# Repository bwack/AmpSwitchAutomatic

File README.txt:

Amp Switch Automatic,
6 amplifiers connected to one pair of stereo speakers with
automatic switching.

Realized with 1970-80s digital logic technology on two stripboards, and
a project box with 28 speaker terminals on it and a 5V power input.

Cheepo auto 1:1 600:600 ohm audio transformers were used to galvanically
isolate the amplifiers, and to pass audio to the detector circuits (lm339).
The relays switch the amplifiers in one at a time. If there is audio on
more than one amplifier, the amp switch sticks to the currently switched amp,
just to keep the box from switching too much. It is not intended to mix,
just switch though.

Bwack, 2017

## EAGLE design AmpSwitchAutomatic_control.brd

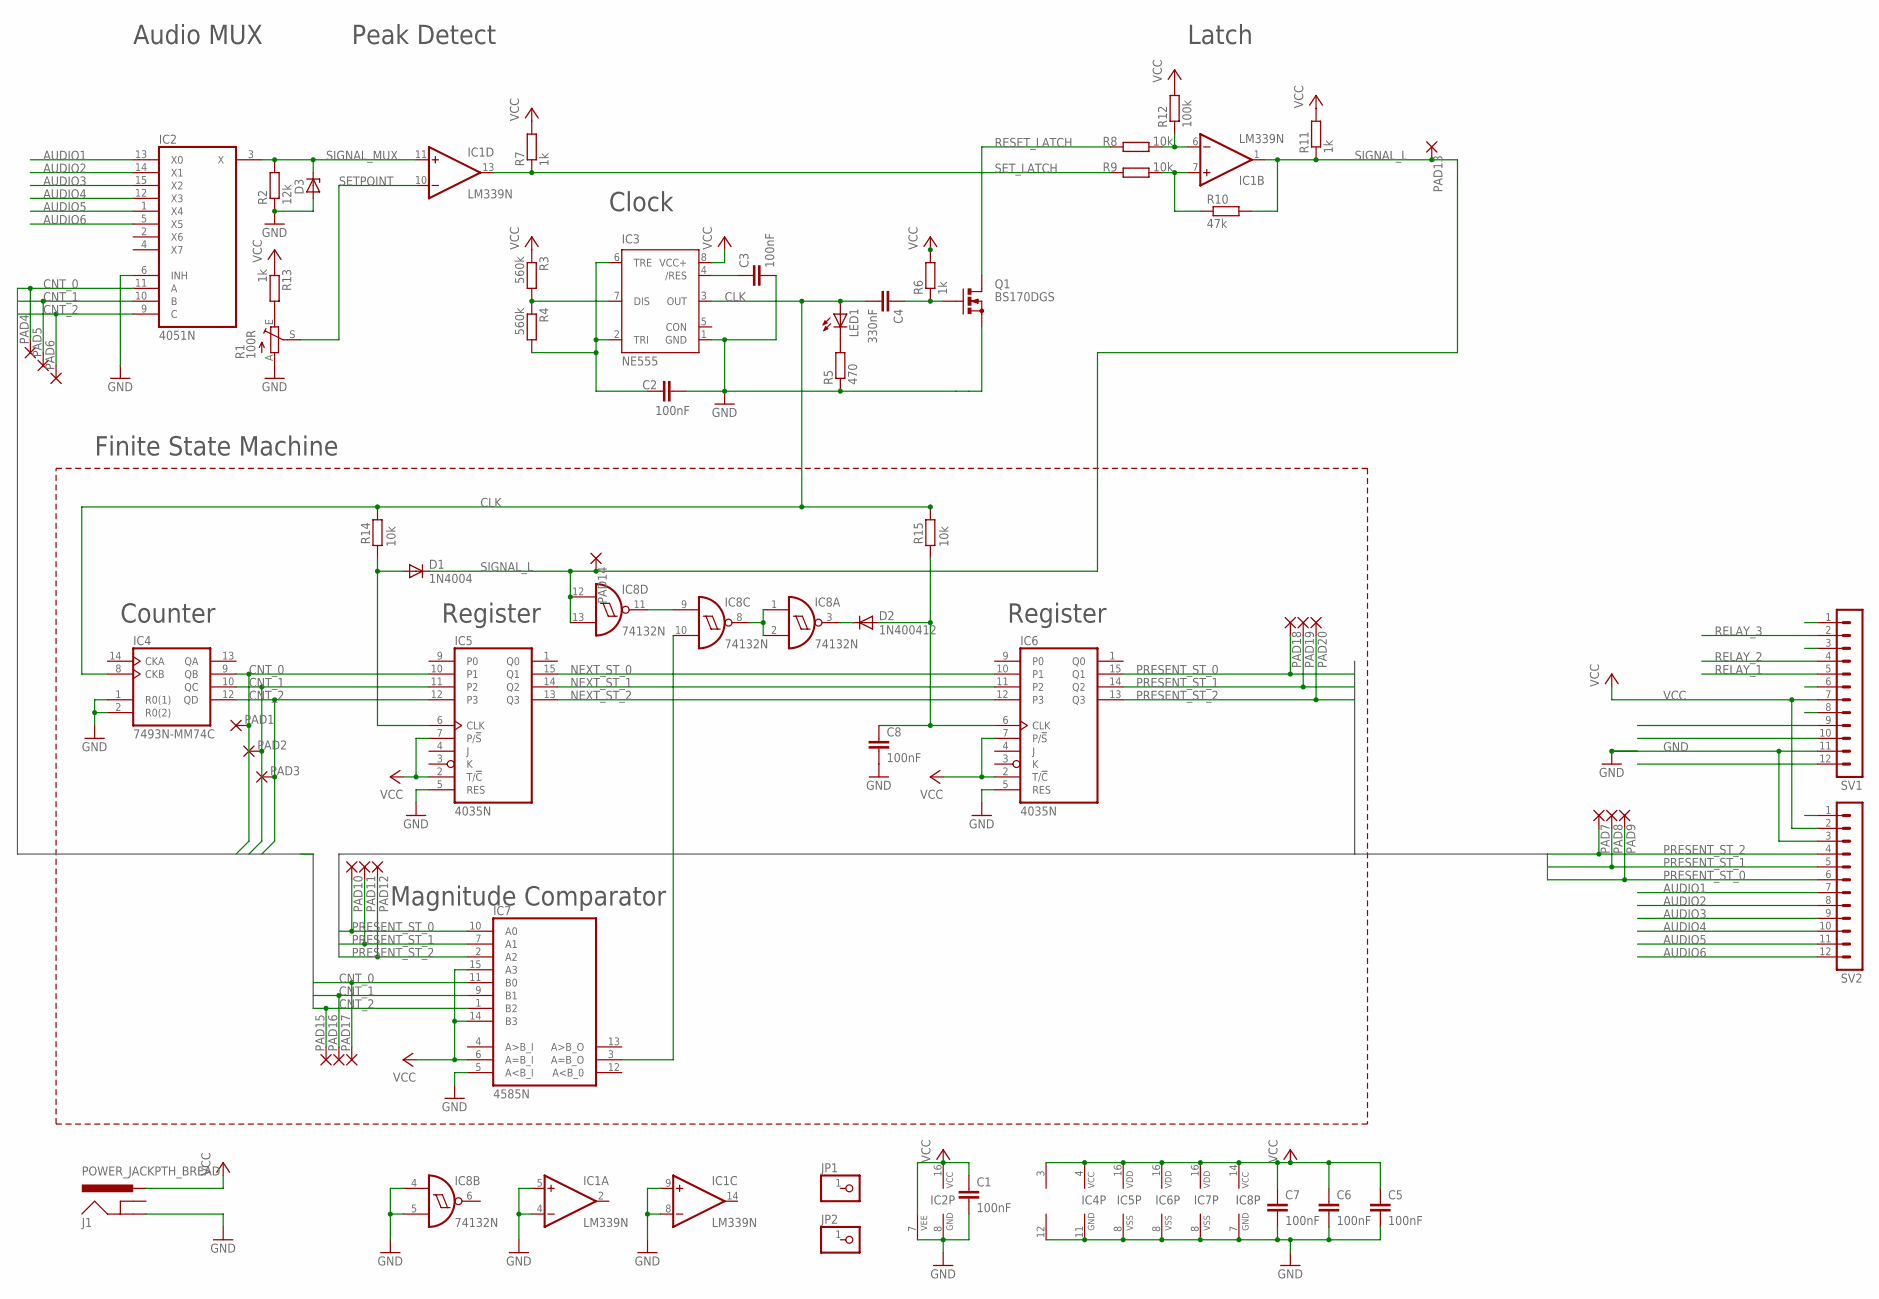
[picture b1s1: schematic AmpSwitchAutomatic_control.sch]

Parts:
C1, C5, C6, C7: 100nF; C025-025X050
C2, C3: 100nF; C025-024X044
C4: 330nF; C075-032X103
C8: 100nF; C050-025X075
D1: 1N4004; DO41-10
D2: 1N400412; DO41-12
D3: ZENER-DIODEDO35Z10; DO35Z10
IC1: LM339N; DIL14
IC2: 4051N; DIL16
IC3: NE555; DIL-08
IC4: 7493N-MM74C; DIL14
IC5, IC6: 4035N; DIL16
IC7: 4585N; DIL16
IC8: 74132N; DIL14
J1: POWER_JACKPTH_BREAD; POWER_JACK_PTH_BREAD
JP1, JP2: PINHD-1X1; 1X01
LED1: LED5MM
PAD1, PAD2, PAD3, PAD4, PAD5, PAD6, PAD7, PAD8, PAD9, PAD10, PAD11, PAD12, PAD13, PAD14, PAD15, PAD16, PAD17, PAD18, PAD19, PAD20: WIREPAD1,6/0,9; 1,6/0,9
Q1: BS170DGS; TO92-LINE
R1: 100R; B25P
R2: 12k; 0207/10
R3, R4: 560k; 0207/2V
R5: 470; 0207/15
R6: 1k; 0207/12
R7, R11: 1k; 0207/5V
R8: 10k; 0207/5V
R9: 10k; 0207/15
R10: 47k; 0207/15
R12: 100k; 0207/7
R13: 1k; 0207/7
R14: 10k; 0207/7
R15: 10k; 0207/2V
SV1, SV2: MA12-1

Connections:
AUDIO1: IC2.13 (X0), SV2.7
AUDIO2: IC2.14 (X1), SV2.8
AUDIO3: IC2.15 (X2), SV2.9
AUDIO4: IC2.12 (X3), SV2.10
AUDIO5: IC2.1 (X4), SV2.11
AUDIO6: IC2.5 (X5), SV2.12
CLK: C4.2, IC3.3 (OUT), IC4.8 (CKB), LED1.A, R14.2, R15.2
CNT_0: IC2.11 (A), IC4.9 (QB), IC5.10 (P1), IC7.11 (B0), PAD1.1, PAD4.1, PAD17.1
CNT_1: IC2.10 (B), IC4.10 (QC), IC5.11 (P2), IC7.9 (B1), PAD2.1, PAD5.1, PAD16.1
CNT_2: IC2.9 (C), IC4.12 (QD), IC5.12 (P3), IC7.1 (B2), PAD3.1, PAD6.1, PAD15.1
GND: C1.2, C2.2, C3.2, C5.2, C6.2, C7.2, C8.2, D3.A, IC1.4 (-IN), IC1.5 (+IN), IC1.8 (-IN), IC1.9 (+IN), IC1.12 (GND), IC2.6 (INH), IC2.7 (VEE), IC2.8 (GND), IC3.1 (GND), IC4.1 (R0(1)), IC4.2 (R0(2)), IC4.11 (GND), IC5.5 (RES), IC5.8 (VSS), IC6.5 (RES), IC6.8 (VSS), IC7.5 (A<B_I), IC7.8 (VSS), IC8.4 (I0), IC8.5 (I1), IC8.7 (GND), J1.GND, Q1.3 (S), R1.A, R2.1, R5.1, SV1.11, SV2.3
unnamed: R1.E, R13.2
unnamed: IC3.7 (DIS), R3.2, R4.1
unnamed: C2.1, IC3.2 (TRI), IC3.6 (TRE), R4.2
unnamed: LED1.K (C), R5.2
unnamed: C4.1, Q1.2 (G), R6.1
unnamed: IC1.6 (-IN), R8.2, R12.1
unnamed: IC1.7 (+IN), R9.2, R10.1
unnamed: C3.1, IC3.4 (/RES)
unnamed: D1.A, IC5.6 (CLK), R14.1
unnamed: D2.C, IC8.3 (O)
unnamed: C8.1, D2.A, IC6.6 (CLK), R15.1
unnamed: IC7.3 (A=B_O), IC8.10 (I1)
unnamed: IC8.1 (I0), IC8.2 (I1), IC8.8 (O)
unnamed: IC8.9 (I0), IC8.11 (O)
NEXT_ST_0: IC5.15 (Q1), IC6.10 (P1)
NEXT_ST_1: IC5.14 (Q2), IC6.11 (P2)
NEXT_ST_2: IC5.13 (Q3), IC6.12 (P3)
PRESENT_ST_0: IC6.15 (Q1), IC7.10 (A0), PAD9.1, PAD10.1, PAD18.1, SV2.6
PRESENT_ST_1: IC6.14 (Q2), IC7.7 (A1), PAD8.1, PAD11.1, PAD19.1, SV2.5
PRESENT_ST_2: IC6.13 (Q3), IC7.2 (A2), PAD7.1, PAD12.1, PAD20.1, SV2.4
RELAY_1: SV1.5
RELAY_2: SV1.4
RELAY_3: SV1.2
RESET_LATCH: Q1.1 (D), R8.1
SETPOINT: IC1.10 (-IN), R1.S
SET_LATCH: IC1.13 (OUT), R7.1, R9.1
SIGNAL_L: D1.C, IC1.1 (OUT), IC8.12 (I0), IC8.13 (I1), PAD13.1, PAD14.1, R10.2, R11.1
SIGNAL_MUX: D3.C, IC1.11 (+IN), IC2.3 (X), R2.2
VCC: C1.1, C5.1, C6.1, C7.1, IC1.3 (V+), IC2.16 (VCC), IC3.8 (VCC+), IC4.4 (VCC), IC5.2 (T/!C), IC5.7 (P/!S), IC5.16 (VDD), IC6.2 (T/!C), IC6.7 (P/!S), IC6.16 (VDD), IC7.6 (A=B_I), IC7.14 (B3), IC7.15 (A3), IC7.16 (VDD), IC8.14 (VCC), J1.PWR, R3.1, R6.2, R7.2, R11.2, R12.2, R13.1, SV1.7, SV2.2

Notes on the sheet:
Audio MUX
Peak Detect
Latch
Clock
Finite State Machine
Counter
Register
Magnitude Comparator

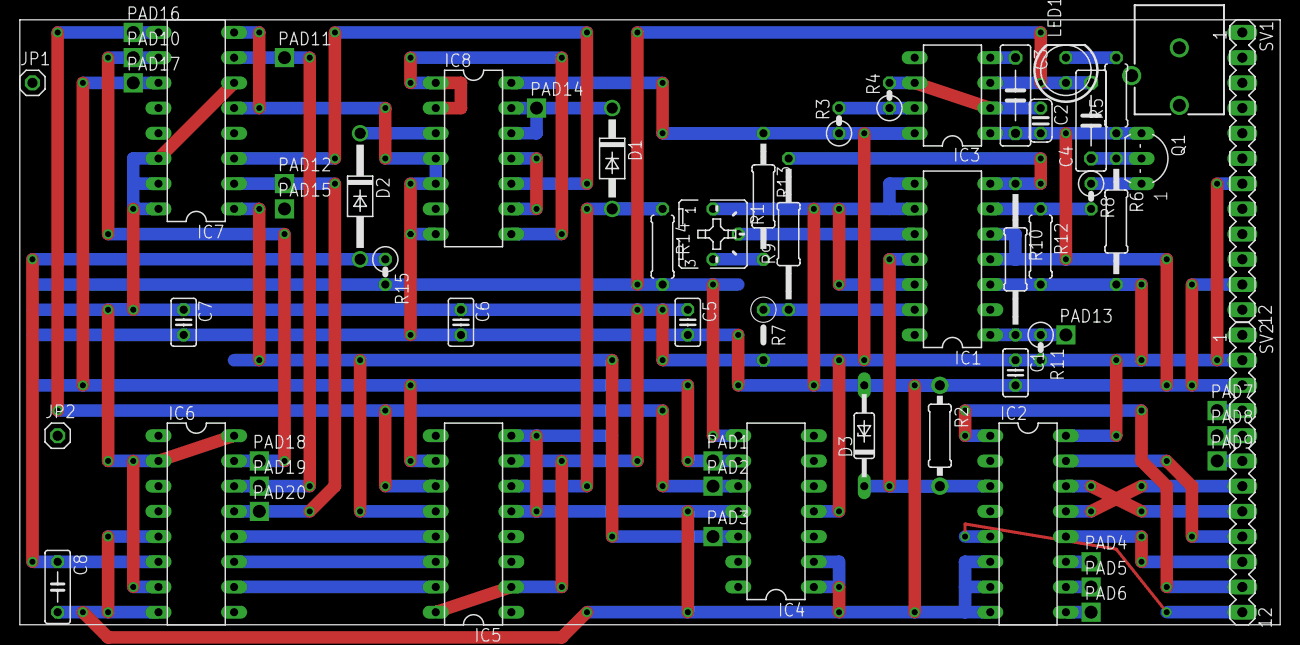
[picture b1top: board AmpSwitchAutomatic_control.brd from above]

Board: 2 copper layers, 127.0 x 61.0 mm, 61 parts (0 on the bottom side), 37 nets.

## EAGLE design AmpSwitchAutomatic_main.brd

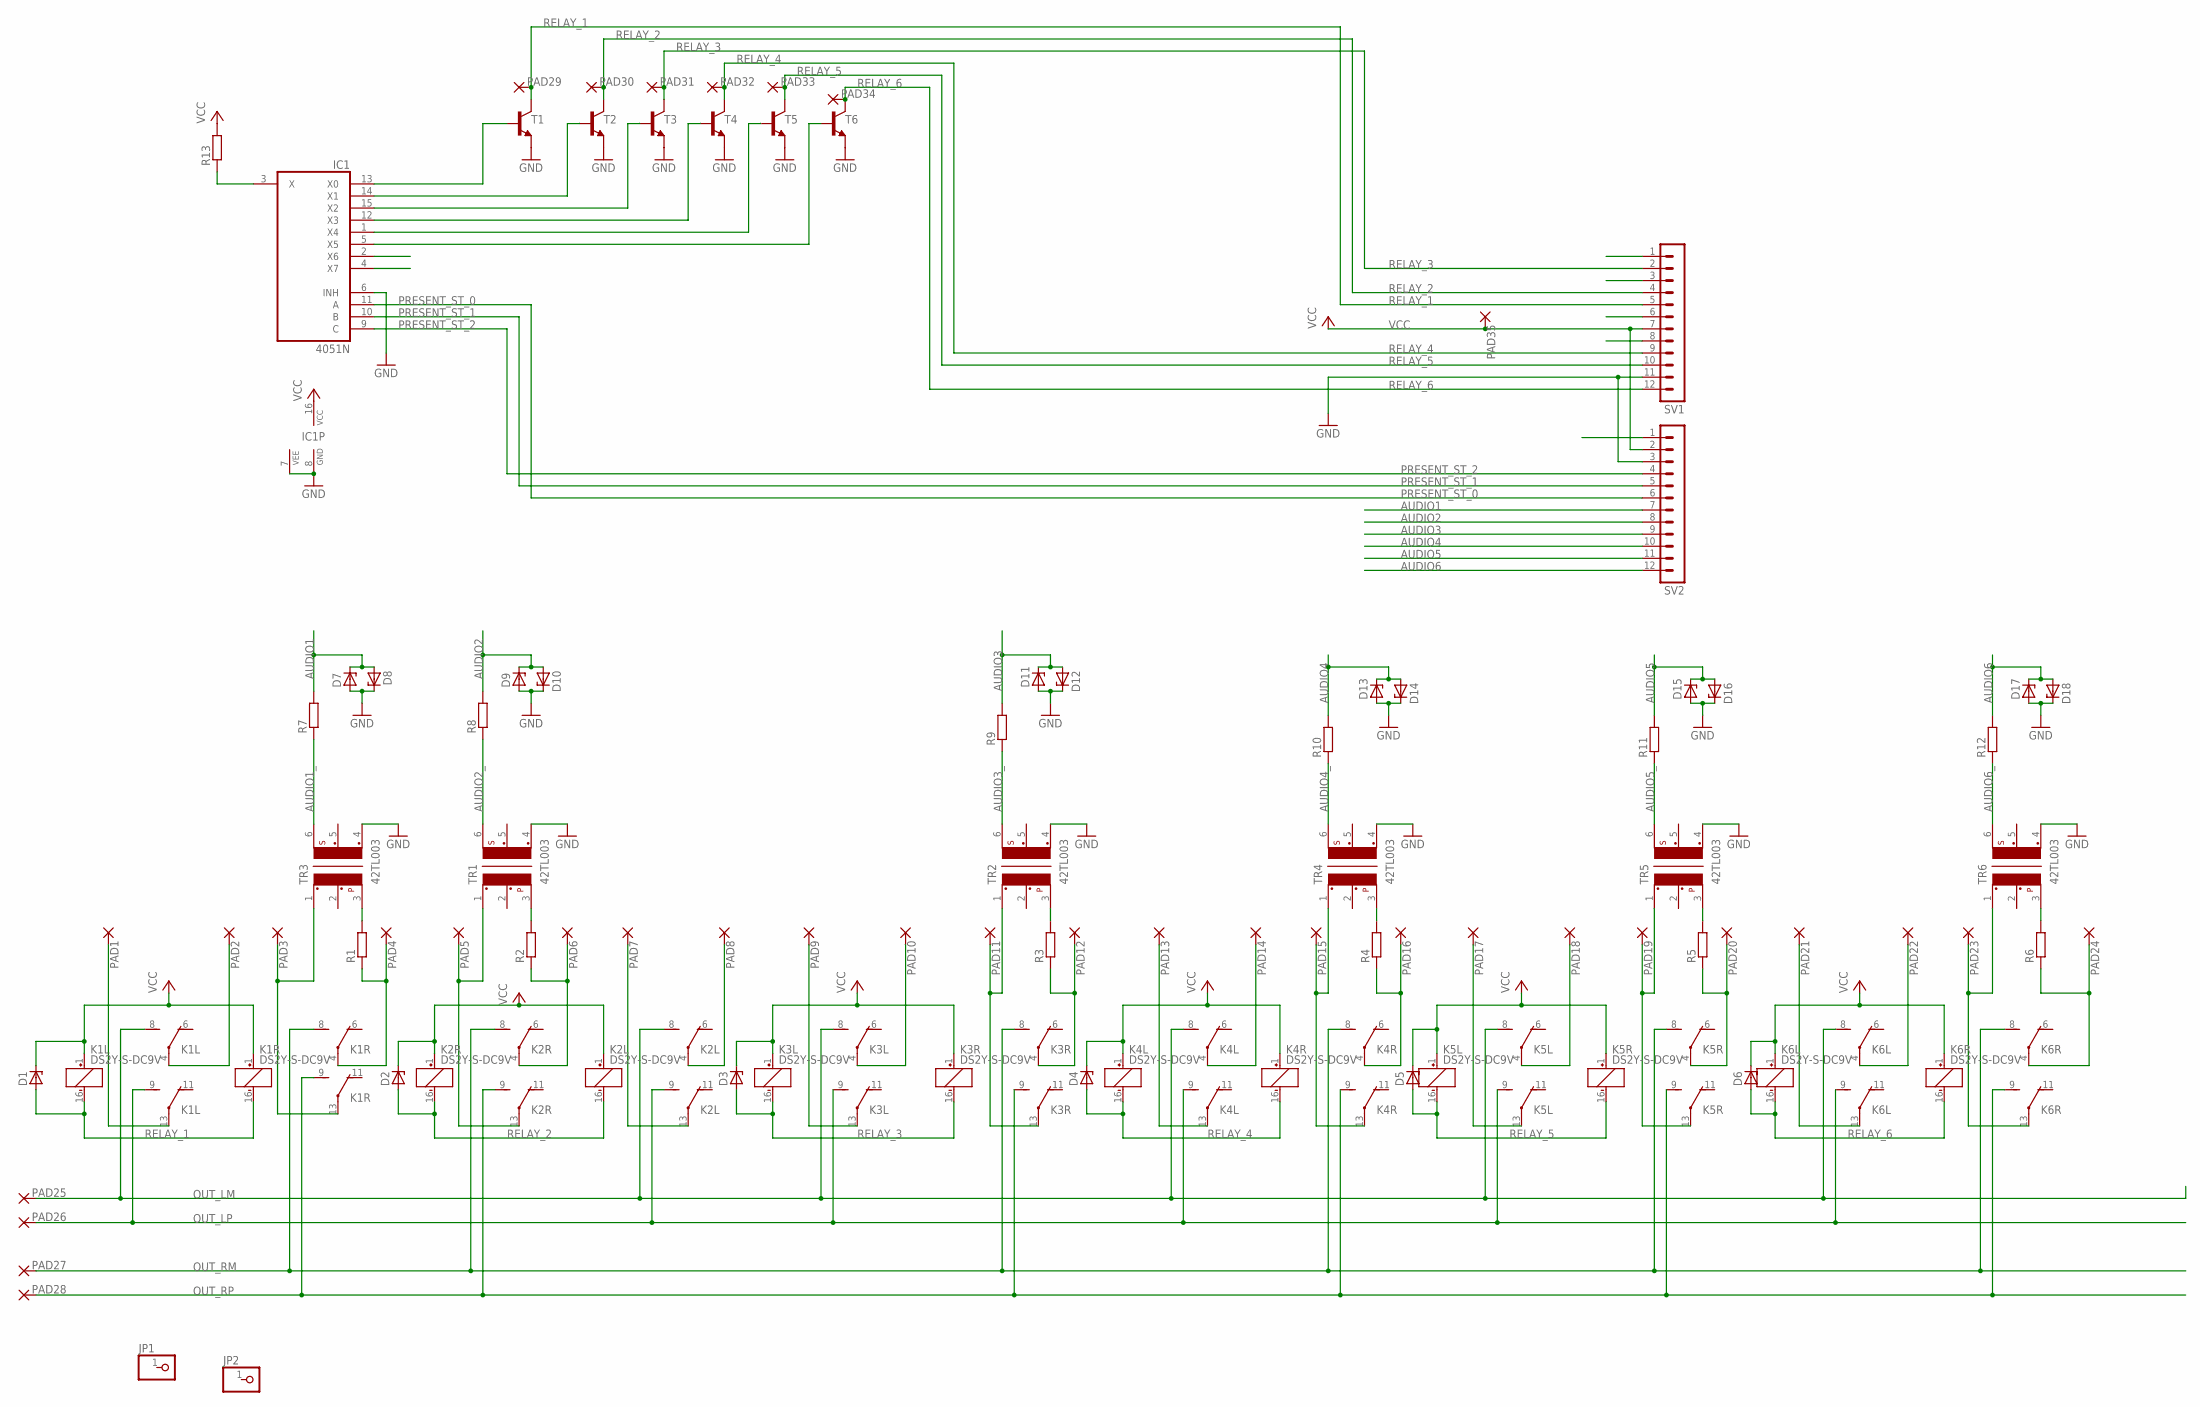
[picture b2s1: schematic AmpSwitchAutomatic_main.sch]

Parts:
D1, D4, D5: ZENER-DIODEZD-5; ZDIO-5
D2, D7, D8, D9, D10, D11, D12, D13, D14, D15, D16, D17, D18: ZENER-DIODEZD-7.5; ZDIO-7.5
D3, D6: ZENER-DIODEZD-12.5; ZDIO12.5
IC1: 4051N; DIL16
JP1, JP2: PINHD-1X1; 1X01
K1L: DS2Y-S-DC9V; DS2Y
K1R, K2L, K2R, K3L, K3R, K4L, K4R, K5L, K5R, K6L, K6R: DS2Y-S-DC9V; DS2Y; MPN DS2Y-S-DC9V
PAD1, PAD2, PAD3, PAD4, PAD5, PAD6, PAD7, PAD8, PAD9, PAD10, PAD11, PAD12, PAD13, PAD14, PAD15, PAD16, PAD17, PAD18, PAD19, PAD20, PAD21, PAD22, PAD23, PAD24, PAD25, PAD26, PAD27, PAD28, PAD29, PAD30, PAD31, PAD32, PAD33, PAD34, PAD35: WIREPAD2,15/1,0; 2,15/1,0
R1, R2, R3, R4, R5, R6: R-EU_0207/15; 0207/15
R7: R-EU_0207/12; 0207/12
R8: R-EU_0207/10; 0207/10
R9, R13: R-EU_0207/7; 0207/7
R10, R12: R-EU_0207/5V; 0207/5V
R11: R-EU_0207/2V; 0207/2V
SV1, SV2: MA12-1
T1, T2, T3, T4, T5, T6: 2N4124-NPN-TO92-CBE; TO92-CBE
TR1, TR2, TR3, TR4, TR5, TR6: 42TL003; 42TL

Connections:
AUDIO1: D7.C, D8.A, R7.2, SV2.7
AUDIO1_: R7.1, TR3.6
AUDIO2: D9.C, D10.A, R8.2, SV2.8
AUDIO2_: R8.1, TR1.6
AUDIO3: D11.C, D12.A, R9.2, SV2.9
AUDIO3_: R9.1, TR2.6
AUDIO4: D13.C, D14.A, R10.2, SV2.10
AUDIO4_: R10.1, TR4.6
AUDIO5: D15.C, D16.A, R11.2, SV2.11
AUDIO5_: R11.1, TR5.6
AUDIO6: D17.C, D18.A, R12.2, SV2.12
AUDIO6_: R12.1, TR6.6
GND: D7.A, D8.C, D9.A, D10.C, D11.A, D12.C, D13.A, D14.C, D15.A, D16.C, D17.A, D18.C, IC1.6 (INH), IC1.7 (VEE), IC1.8 (GND), SV1.11, SV2.3, T1.E, T2.E, T3.E, T4.E, T5.E, T6.E, TR1.4, TR2.4, TR3.4, TR4.4, TR5.4, TR6.4
unnamed: K3R.4, PAD12.1, R3.1
unnamed: K4L.13, PAD13.1
unnamed: K1L.13, PAD1.1
unnamed: K2L.13, PAD7.1
unnamed: K1L.4, PAD2.1
unnamed: K3L.13, PAD9.1
unnamed: K1R.13, PAD3.1, TR3.1
unnamed: K1R.4, PAD4.1, R1.1
unnamed: K3L.4, PAD10.1
unnamed: K4L.4, PAD14.1
unnamed: K2R.13, PAD5.1, TR1.1
unnamed: R1.2, TR3.3
unnamed: R2.2, TR1.3
unnamed: R3.2, TR2.3
unnamed: K3R.13, PAD11.1, TR2.1
unnamed: K2R.4, PAD6.1, R2.1
unnamed: R4.2, TR4.3
unnamed: K4R.13, PAD15.1, TR4.1
unnamed: K4R.4, PAD16.1, R4.1
unnamed: R5.2, TR5.3
unnamed: K2L.4, PAD8.1
unnamed: R6.2, TR6.3
unnamed: IC1.3 (X), R13.1
unnamed: IC1.13 (X0), T1.B
unnamed: IC1.14 (X1), T2.B
unnamed: K5L.13, PAD17.1
unnamed: K5L.4, PAD18.1
unnamed: K5R.13, PAD19.1, TR5.1
unnamed: K5R.4, PAD20.1, R5.1
unnamed: K6L.13, PAD21.1
unnamed: K6L.4, PAD22.1
unnamed: K6R.13, PAD23.1, TR6.1
unnamed: K6R.4, PAD24.1, R6.1
unnamed: IC1.15 (X2), T3.B
unnamed: IC1.12 (X3), T4.B
unnamed: IC1.1 (X4), T5.B
unnamed: IC1.5 (X5), T6.B
OUT_LM: K1L.8 (S), K2L.8 (S), K3L.8 (S), K4L.8 (S), K5L.8 (S), K6L.8 (S), PAD25.1
OUT_LP: K1L.9 (S), K2L.9 (S), K3L.9 (S), K4L.9 (S), K5L.9 (S), K6L.9 (S), PAD26.1
OUT_RM: K1R.8 (S), K2R.8 (S), K3R.8 (S), K4R.8 (S), K5R.8 (S), K6R.8 (S), PAD27.1
OUT_RP: K1R.9 (S), K2R.9 (S), K3R.9 (S), K4R.9 (S), K5R.9 (S), K6R.9 (S), PAD28.1
PRESENT_ST_0: IC1.11 (A), SV2.6
PRESENT_ST_1: IC1.10 (B), SV2.5
PRESENT_ST_2: IC1.9 (C), SV2.4
RELAY_1: D1.A, K1L.16 (-), K1R.16 (-), PAD29.1, SV1.5, T1.C
RELAY_2: D2.A, K2L.16 (-), K2R.16 (-), PAD30.1, SV1.4, T2.C
RELAY_3: D3.A, K3L.16 (-), K3R.16 (-), PAD31.1, SV1.2, T3.C
RELAY_4: D4.A, K4L.16 (-), K4R.16 (-), PAD32.1, SV1.9, T4.C
RELAY_5: D5.A, K5L.16 (-), K5R.16 (-), PAD33.1, SV1.10, T5.C
RELAY_6: D6.A, K6L.16 (-), K6R.16 (-), PAD34.1, SV1.12, T6.C
VCC: D1.C, D2.C, D3.C, D4.C, D5.C, D6.C, IC1.16 (VCC), K1L.1 (+), K1R.1 (+), K2L.1 (+), K2R.1 (+), K3L.1 (+), K3R.1 (+), K4L.1 (+), K4R.1 (+), K5L.1 (+), K5R.1 (+), K6L.1 (+), K6R.1 (+), PAD35.1, R13.2, SV1.7, SV2.2

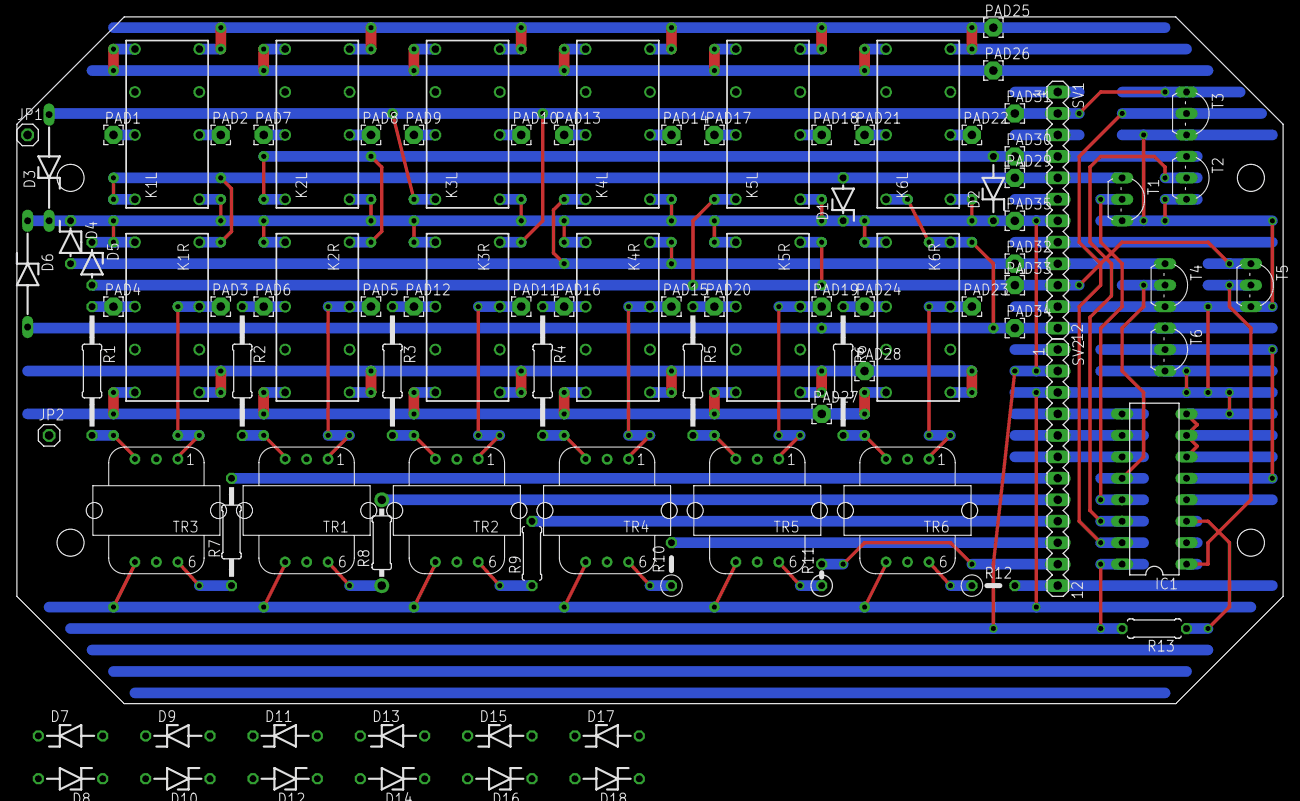
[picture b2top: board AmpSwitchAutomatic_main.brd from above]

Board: 2 copper layers, 149.9 x 81.3 mm, 95 parts (0 on the bottom side), 64 nets.

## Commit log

2017-02-18 :octocat: Added .gitattributes & .gitignore files
2017-02-18 gitignore
2017-03-18 Finalized

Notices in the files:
parts and their libraries:
SparkFun-Connectors: Licensing: Creative Commons ShareAlike 4.0 International - https://creativecommons.org/licenses/by-sa/4.0
